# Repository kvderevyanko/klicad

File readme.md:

# Несущая плата ESP32 + E220, Rev.1

Текущая Rev.1 — **кандидат для предсерийной проверки**, а не производственный выпуск. Электрическая схема и трассировка завершены: 37 посадочных мест, 200 дорожек, 58 переходных отверстий, четыре медные зоны, два слоя, контур 145 × 90 мм; ERC, native DRC, соответствие схемы/платы и контракт платы проходят без ошибок и без неподключённых объектов.

## Действующая архитектура питания

\`BAT_PLUS → F1 → BAT_FUSED → J8.1 → внешний выключатель → J8.2 → BAT_SW → Q1 → BUCK_IN → TPS62133 → 5V_SYS\`.

\`D3 SMBJ10CA\` подключён между \`BAT_FUSED\` и GND. У Q1 \`DMP3130LQ-7\`: 1=\`Q1_GATE\`, 2=\`BUCK_IN\`, 3=\`BAT_SW\`.

\`5V_SYS → JP1 → VIN ESP32 DevKit\`. Обычный режим: выключатель включён, JP1 замкнут. Для сервисного USB с изоляцией: выключатель выключен, JP1 разомкнут при необходимости; JP1 не является автоматической изоляцией доменов.

\`5V_SYS → U4 TLV1117LV33 → AUX_3V3 → OLED\`. OLED питается только от \`AUX_3V3\`; \`DEVKIT_3V3\` не является питанием аксессуаров.

## Узлы и сборка

- J1/J2 — заводски устанавливаемые розетки ESP32; сам ESP32 DevKit устанавливает пользователь.
- J3 — заводски устанавливаемая розетка Samtec для одного пользовательского E220-400T22D или E220-900T22D; антенна обязана соответствовать диапазону модуля.
- J5 — заводски устанавливаемая розетка OLED; механическая совместимость конкретного OLED подтверждается на первом образце.
- J6 \`BUTTONS\` и J9 \`RGB OUT\` — пользовательские DNP-интерфейсы.
- D2, J7 и TP6…TP10 отсутствуют. TP1…TP5 — сохранённые металлизированные пробные отверстия без устанавливаемого компонента.

Электрические соединения завершены. Крепёж и разгрузка аккумуляторного кабеля сознательно отложены до корпуса/жгута или Rev.2. Генерация Gerber, сверловки, производственного BOM и CPL разрешается только отдельной задачей после предсерийного ревью.

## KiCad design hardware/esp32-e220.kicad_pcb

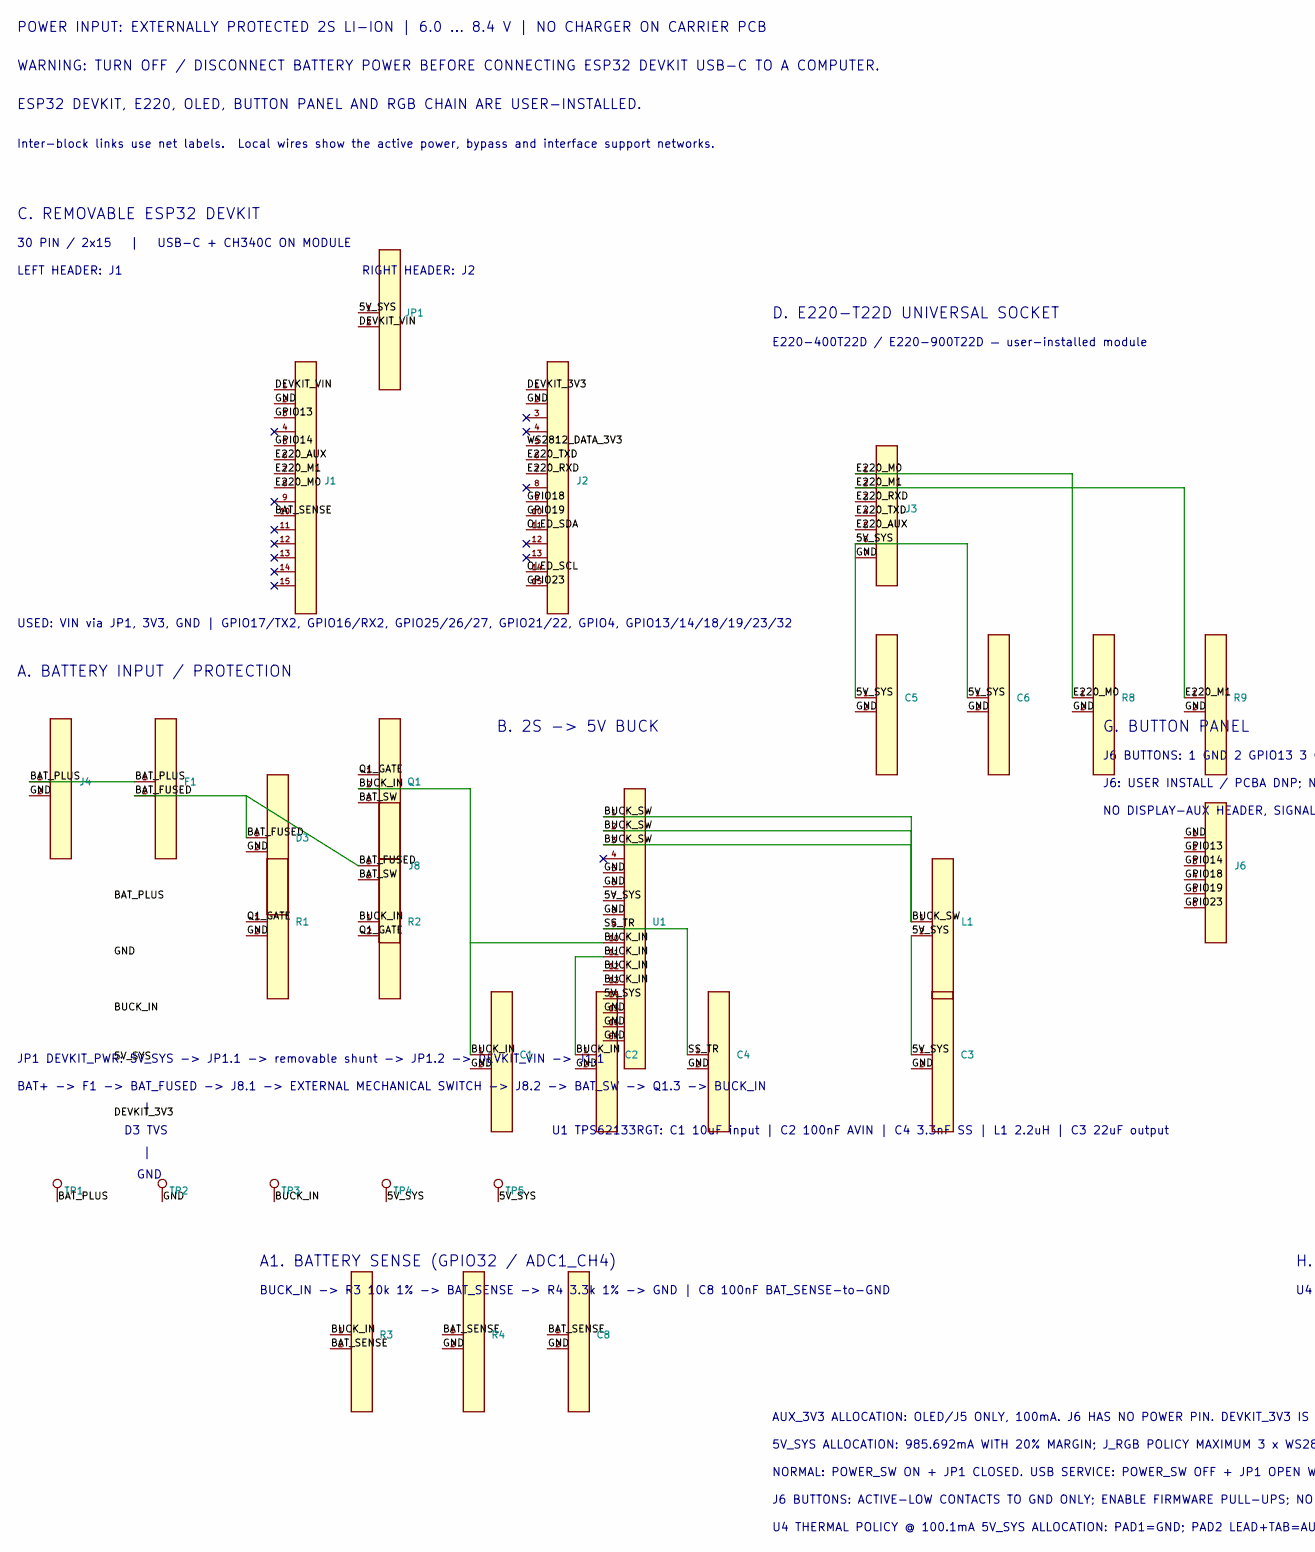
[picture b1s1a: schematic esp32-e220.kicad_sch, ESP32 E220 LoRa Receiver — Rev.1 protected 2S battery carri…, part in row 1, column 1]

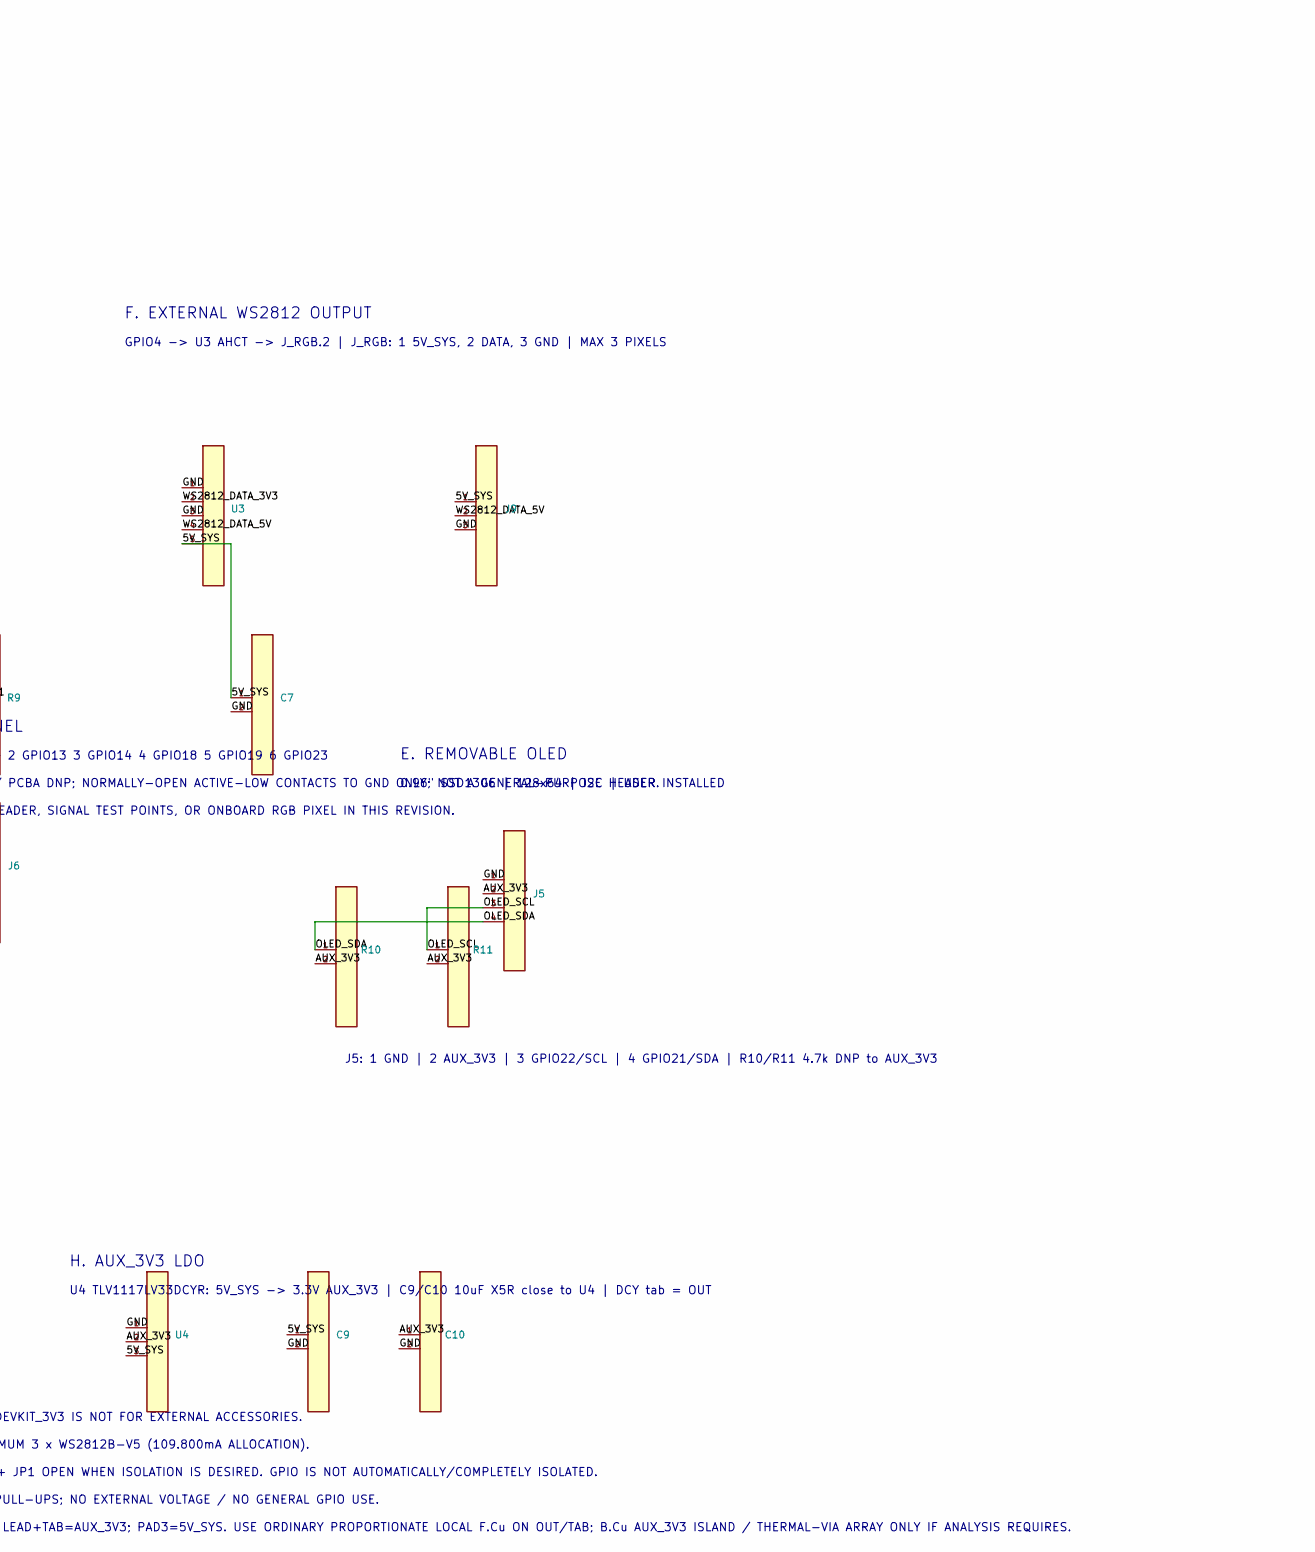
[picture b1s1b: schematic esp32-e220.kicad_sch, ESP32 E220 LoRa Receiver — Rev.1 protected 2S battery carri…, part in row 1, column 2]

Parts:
C1, C9, C10: GRM21BR61E106KA73; Murata_GRM21_2012Metric
C2, C6, C7, C8: GRM188R71C104KA01D; Murata_GRM188_1608Metric
C3: GRM21BR61A226ME44; Murata_GRM21_2012Metric
C4: GRM1885C1H332JA01D; Murata_GRM188_1608Metric
C5: GRM188R61A106MAAL; Murata_GRM188_1608Metric
D3: SMBJ10CA; Littelfuse_SMBJ10CA_DO214AA
F1: 1812L200/16; Littelfuse_1812L200_16_4532Metric
J1: SSW-115-02-G-S DEVKIT LEFT; Samtec_SSW_1x15_P2.54mm_THT
J2: SSW-115-02-G-S DEVKIT RIGHT; Samtec_SSW_1x15_P2.54mm_THT
J3: E220-400T22D / E220-900T22D SOCKET; E220_T22D_Socket_400_900
J4, J8: B2B-XH-A; JST_B2B-XH-A_1x02_P2.50mm_THT
J5: SSW-104-02-G-S; Samtec_SSW_1x04_P2.54mm_THT
J6: BUTTONS 1x6 2.54mm DNP; PinHeader_1x06_P2.54mm_Vertical
J9: J_RGB / RGB OUT 1x3 2.54mm DNP; PinHeader_1x03_P2.54mm_Vertical
JP1: TSW-102-07-G-S + SNT-100-BK-G; PinHeader_1x02_P2.54mm_Vertical
L1: XFL4020-222MEB; Coilcraft_XFL4020-222MEB
Q1: DMP3130LQ-7; Diodes_DMP3130LQ-7_SOT23
R1: 100k 1%; Resistor_0603_1608Metric
R2: 1M 1%; Resistor_0603_1608Metric
R3: RC0603FR-0710KL; Resistor_0603_1608Metric
R4: RC0603FR-073K3L; Resistor_0603_1608Metric
R8, R9: 10k 1%; Resistor_0603_1608Metric
R10: DNP 4.7k 1% OLED SDA pull-up to AUX_3V3
R11: DNP 4.7k 1% OLED SCL pull-up to AUX_3V3
TP1: BAT_PLUS; TestPoint_THT_1p0mm_PROTOTYPE
TP2: GND; TestPoint_THT_1p0mm_PROTOTYPE
TP3: BUCK_IN; TestPoint_THT_1p0mm_PROTOTYPE
TP4, TP5: 5V_SYS; TestPoint_THT_1p0mm_PROTOTYPE
U1: TPS62133RGT; TI_TPS62133RGT_RGT0016C
U3: SN74AHCT1G125DBVR; TI_SN74AHCT1G125DBVR_SOT23-5
U4: TLV1117LV33DCYR; SOT-223-3_TabPin2

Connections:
/AUX_3V3: C10.1, J5.2 (VCC / 3V3), R10.2, R11.2, U4.2 (OUT / TAB)
/BAT_FUSED: D3.1 (A), F1.2, J8.1 (BAT_FUSED)
/BAT_PLUS: F1.1, J4.1 (BAT+), TP1.1
/BAT_SENSE: C8.1, J1.10 (GPIO32), R3.2, R4.1
/BAT_SW: J8.2 (BAT_SW), Q1.3 (D)
/BUCK_IN: C1.1, C2.1, Q1.2 (S), R2.1, R3.1, TP3.1, U1.10 (AVIN), U1.11 (PVIN), U1.12 (PVIN), U1.13 (EN)
/BUCK_SW: L1.1, U1.1 (SW), U1.2 (SW), U1.3 (SW)
/DEVKIT_3V3: J2.1 (3V3)
/DEVKIT_VIN: J1.1 (VIN / 5V), JP1.2 (DEVKIT_VIN)
/E220_AUX: J1.6 (GPIO27), J3.5 (AUX)
/E220_M0: J1.8 (GPIO25), J3.1 (M0), R8.1
/E220_M1: J1.7 (GPIO26), J3.2 (M1), R9.1
/E220_RXD: J2.7 (GPIO17/TX2), J3.3 (RXD)
/E220_TXD: J2.6 (GPIO16/RX2), J3.4 (TXD)
/GPIO13: J1.3 (GPIO13), J6.2 (GPIO13)
/GPIO14: J1.5 (GPIO14), J6.3 (GPIO14)
/GPIO18: J2.9 (GPIO18), J6.4 (GPIO18)
/GPIO19: J2.10 (GPIO19), J6.5 (GPIO19)
/GPIO23: J2.15 (GPIO23), J6.6 (GPIO23)
/OLED_SCL: J2.14 (GPIO22), J5.3 (SCL), R11.1
/OLED_SDA: J2.11 (GPIO21), J5.4 (SDA), R10.1
/Q1_GATE: Q1.1 (G), R1.1, R2.2
/SS_TR: C4.1, U1.9 (SS/TR)
/WS2812_DATA_3V3: J2.5 (GPIO4), U3.2 (A)
/WS2812_DATA_5V: J9.2 (WS2812_DATA_5V), U3.4 (Y)

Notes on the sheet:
A. BATTERY INPUT / PROTECTION
B. 2S -> 5V BUCK
H. AUX_3V3 LDO
U4 TLV1117LV33DCYR: 5V_SYS -> 3.3V AUX_3V3 | C9/C10 10uF X5R close to U4 | DCY tab = OUT
AUX_3V3 ALLOCATION: OLED/J5 ONLY, 100mA. J6 HAS NO POWER PIN. DEVKIT_3V3 IS NOT FOR EXTERNAL ACCESSORIES.
5V_SYS ALLOCATION: 985.692mA WITH 20% MARGIN; J_RGB POLICY MAXIMUM 3 x WS2812B-V5 (109.800mA ALLOCATION).
NORMAL: POWER_SW ON + JP1 CLOSED. USB SERVICE: POWER_SW OFF + JP1 OPEN WHEN ISOLATION IS DESIRED. GPIO IS NOT AUTOMATICALLY/COMPLETELY ISOLATED.
J6 BUTTONS: ACTIVE-LOW CONTACTS TO GND ONLY; ENABLE FIRMWARE PULL-UPS; NO EXTERNAL VOLTAGE / NO GENERAL GPIO USE.
U4 THERMAL POLICY @ 100.1mA 5V_SYS ALLOCATION: PAD1=GND; PAD2 LEAD+TAB=AUX_3V3; PAD3=5V_SYS. USE ORDINARY PROPORTIONATE LOCAL F.Cu ON OUT/TAB; B.Cu AUX_3V3 ISLAND / THERMAL-VIA ARRAY ONLY IF ANALYSIS REQUIRES.
A1. BATTERY SENSE (GPIO32 / ADC1_CH4)
BUCK_IN -> R3 10k 1% -> BAT_SENSE -> R4 3.3k 1% -> GND | C8 100nF BAT_SENSE-to-GND
C. REMOVABLE ESP32 DEVKIT
30 PIN / 2x15 | USB-C + CH340C ON MODULE
LEFT HEADER: J1 RIGHT HEADER: J2
USED: VIN via JP1, 3V3, GND | GPIO17/TX2, GPIO16/RX2, GPIO25/26/27, GPIO21/22, GPIO4, GPIO13/14/18/19/23/32
D. E220-T22D UNIVERSAL SOCKET
E220-400T22D / E220-900T22D — user-installed module
F. EXTERNAL WS2812 OUTPUT
GPIO4 -> U3 AHCT -> J_RGB.2 | J_RGB: 1 5V_SYS, 2 DATA, 3 GND | MAX 3 PIXELS
E. REMOVABLE OLED
0.96" SSD1306 | 128x64 | I2C | USER INSTALLED
POWER INPUT: EXTERNALLY PROTECTED 2S LI-ION | 6.0 ... 8.4 V | NO CHARGER ON CARRIER PCB
WARNING: TURN OFF / DISCONNECT BATTERY POWER BEFORE CONNECTING ESP32 DEVKIT USB-C TO A COMPUTER.
ESP32 DEVKIT, E220, OLED, BUTTON PANEL AND RGB CHAIN ARE USER-INSTALLED.
Inter-block links use net labels. Local wires show the active power, bypass and interface support networks.
G. BUTTON PANEL
J6 BUTTONS: 1 GND 2 GPIO13 3 GPIO14 4 GPIO18 5 GPIO19 6 GPIO23
J6: USER INSTALL / PCBA DNP; NORMALLY-OPEN ACTIVE-LOW CONTACTS TO GND ONLY; NOT A GENERAL-PURPOSE HEADER.
NO DISPLAY-AUX HEADER, SIGNAL TEST POINTS, OR ONBOARD RGB PIXEL IN THIS REVISION.
JP1 DEVKIT_PWR: 5V_SYS -> JP1.1 -> removable shunt -> JP1.2 -> DEVKIT_VIN -> J1.1
BAT+ -> F1 -> BAT_FUSED -> J8.1 -> EXTERNAL MECHANICAL SWITCH -> J8.2 -> BAT_SW -> Q1.3 -> BUCK_IN
D3 TVS
GND
U1 TPS62133RGT: C1 10uF input | C2 100nF AVIN | C4 3.3nF SS | L1 2.2uH | C3 22uF output
J5: 1 GND | 2 AUX_3V3 | 3 GPIO22/SCL | 4 GPIO21/SDA | R10/R11 4.7k DNP to AUX_3V3

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
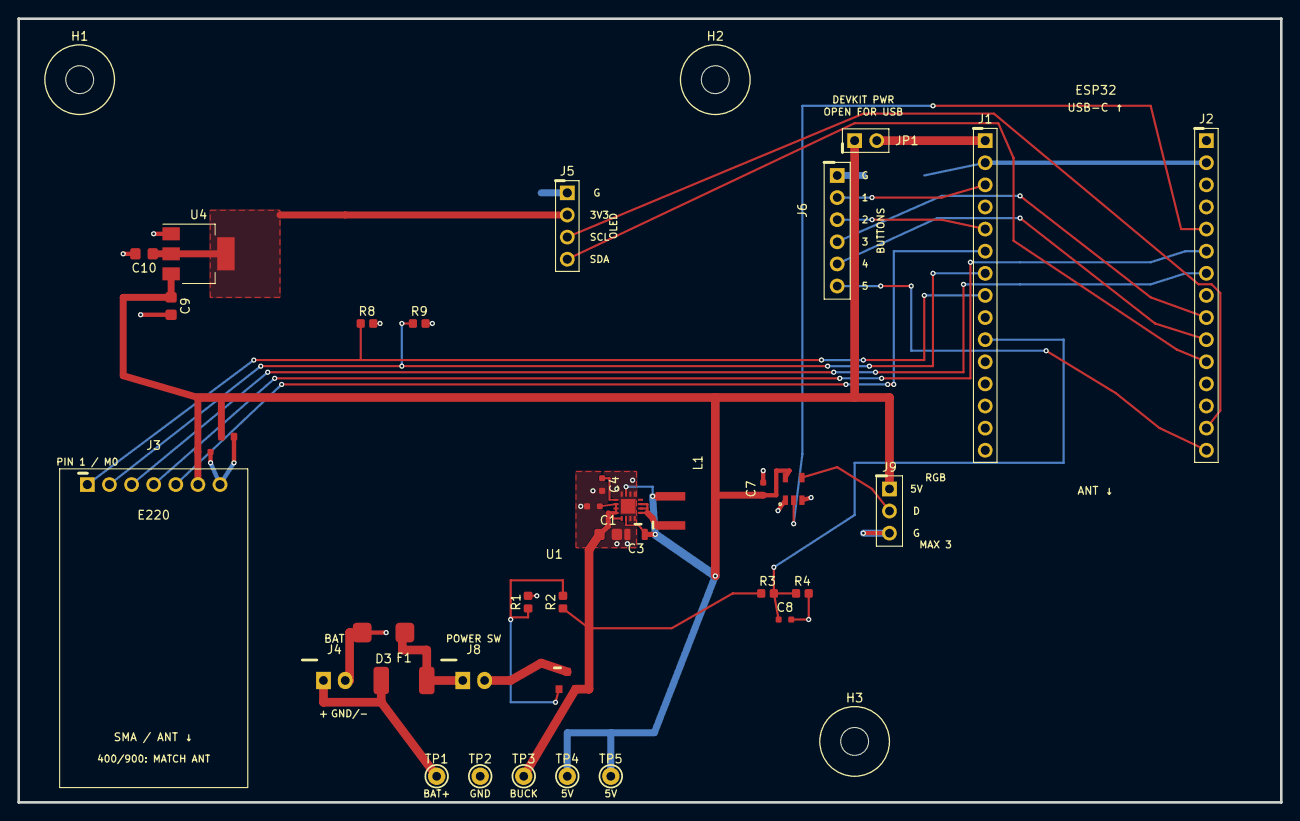
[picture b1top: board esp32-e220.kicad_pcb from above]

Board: 2 copper layers, 145.0 x 90.0 mm, 40 parts (0 on the bottom side), 26 nets.

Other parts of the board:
H1, H2, H3: M3 NPTH; MountingHole_M3_NPTH_REV1

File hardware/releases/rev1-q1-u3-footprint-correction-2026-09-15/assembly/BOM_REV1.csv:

Item,Qty,References,Value,Manufacturer,MPN,Footprint,AssemblyClass,ProcurementPolicy,Notes
1,1,R1,100k 1%,,,Resistor_0603_1608Metric,PCBA_POPULATE,APPROVED_GENERIC,
2,2,"R8, R9",10k 1%,,,Resistor_0603_1608Metric,PCBA_POPULATE,APPROVED_GENERIC,
3,1,F1,1812L200/16,Littelfuse,1812L200/16,Littelfuse_1812L200_16_4532Metric,PCBA_POPULATE,EXACT_MPN,
4,1,R2,1M 1%,,,Resistor_0603_1608Metric,PCBA_POPULATE,APPROVED_GENERIC,
5,2,"J4, J8",B2B-XH-A,JST,B2B-XH-A,JST_B2B-XH-A_1x02_P2.50mm_THT,PCBA_POPULATE,EXACT_MPN,
6,1,Q1,DMP3130LQ-7,Diodes Incorporated,DMP3130LQ-7,Diodes_DMP3130LQ-7_SOT23,PCBA_POPULATE,EXACT_MPN,
7,1,J3,E220-400T22D / E220-900T22D SOCKET,Samtec,SSW-107-02-G-S,E220_T22D_Socket_400_900,PCBA_POPULATE,EXACT_MPN,"E220 carrier socket, not E220 module"
8,1,C4,GRM1885C1H332JA01D,Murata,GRM1885C1H332JA01D,Murata_GRM188_1608Metric,PCBA_POPULATE,EXACT_MPN,
9,1,C5,GRM188R61A106MAAL,Murata,GRM188R61A106MAAL,Murata_GRM188_1608Metric,PCBA_POPULATE,EXACT_MPN,
10,1,C8,GRM188R71C104KA01D,Murata,GRM188R71C104KA01D,Carrier:Murata_GRM188_1608Metric,PCBA_POPULATE,EXACT_MPN,
11,3,"C2, C6, C7",GRM188R71C104KA01D,Murata,GRM188R71C104KA01D,Murata_GRM188_1608Metric,PCBA_POPULATE,EXACT_MPN,
12,1,C3,GRM21BR61A226ME44,Murata,GRM21BR61A226ME44,Murata_GRM21_2012Metric,PCBA_POPULATE,EXACT_MPN,
13,2,"C10, C9",GRM21BR61E106KA73,Murata,GRM21BR61E106KA73,Carrier:Murata_GRM21_2012Metric,PCBA_POPULATE,EXACT_MPN,
14,1,C1,GRM21BR61E106KA73,Murata,GRM21BR61E106KA73,Murata_GRM21_2012Metric,PCBA_POPULATE,EXACT_MPN,
15,1,R3,RC0603FR-0710KL,Yageo,RC0603FR-0710KL,Carrier:Resistor_0603_1608Metric,PCBA_POPULATE,EXACT_MPN,
16,1,R4,RC0603FR-073K3L,Yageo,RC0603FR-073K3L,Carrier:Resistor_0603_1608Metric,PCBA_POPULATE,EXACT_MPN,
17,1,D3,SMBJ10CA,Littelfuse,SMBJ10CA,Littelfuse_SMBJ10CA_DO214AA,PCBA_POPULATE,EXACT_MPN,
18,1,U3,SN74AHCT1G125DBVR,Texas Instruments,SN74AHCT1G125DBVR,TI_SN74AHCT1G125DBVR_SOT23-5,PCBA_POPULATE,EXACT_MPN,
19,1,J5,SSW-104-02-G-S,Samtec,SSW-104-02-G-S,Samtec_SSW_1x04_P2.54mm_THT,PCBA_POPULATE,EXACT_MPN,"OLED carrier socket, not OLED module"
20,1,J1,SSW-115-02-G-S DEVKIT LEFT,Samtec,SSW-115-02-G-S,Samtec_SSW_1x15_P2.54mm_THT,PCBA_POPULATE,EXACT_MPN,"ESP32 carrier socket, not module"
21,1,J2,SSW-115-02-G-S DEVKIT RIGHT,Samtec,SSW-115-02-G-S,Samtec_SSW_1x15_P2.54mm_THT,PCBA_POPULATE,EXACT_MPN,"ESP32 carrier socket, not module"
22,1,U4,TLV1117LV33DCYR,Texas Instruments,TLV1117LV33DCYR,Package_TO_SOT_SMD:SOT-223-3_TabPin2,PCBA_POPULATE,EXACT_MPN,
23,1,U1,TPS62133RGT,Texas Instruments,TPS62133RGT,TI_TPS62133RGT_RGT0016C,PCBA_POPULATE,EXACT_MPN,
24,1,JP1,TSW-102-07-G-S + SNT-100-BK-G,Samtec,TSW-102-07-G-S,Connector_PinHeader_2.54mm:PinHeader_1x02_P2.54mm_Vertical,PCBA_POPULATE,EXACT_MPN,2-pin header only
25,1,L1,XFL4020-222MEB,Coilcraft,XFL4020-222MEB,Coilcraft_XFL4020-222MEB,PCBA_POPULATE,EXACT_MPN,

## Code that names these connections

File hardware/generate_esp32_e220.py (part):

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def pin_no_connect(center_x, center_y, pin_count, pin_number):
    return no_connect(*pin_pos(center_x, center_y, pin_count, pin_number))

left = [("1","VIN / 5V"),("2","GND"),("3","GPIO13"),("4","GPIO12"),("5","GPIO14"),
        ("6","GPIO27"),("7","GPIO26"),("8","GPIO25"),("9","GPIO33"),("10","GPIO32"),
        ("11","GPIO35"),("12","GPIO34"),("13","GPIO39/VN"),("14","GPIO36/VP"),("15","EN")]
right = [("1","3V3"),("2","GND"),("3","GPIO15"),("4","GPIO2"),("5","GPIO4"),
         ("6","GPIO16/RX2"),("7","GPIO17/TX2"),("8","GPIO5"),("9","GPIO18"),("10","GPIO19"),
         ("11","GPIO21"),("12","GPIO3/RX0"),("13","GPIO1/TX0"),("14","GPIO22"),("15","GPIO23")]
e220 = [("1","M0","input"),("2","M1","input"),("3","RXD","input"),
        ("4","TXD","output"),("5","AUX","output"),("6","VCC","power_in"),("7","GND","power_in")]
oled_i2c = [("1","GND","power_in"),("2","VCC / 3V3","power_in"),
            ("3","SCL","bidirectional"),("4","SDA","bidirectional")]
battery = [("1","BAT+","passive"),("2","BAT-","passive")]
buttons = [("1","GND"),("2","GPIO13"),("3","GPIO14"),("4","GPIO18"),
           ("5","GPIO19"),("6","GPIO23")]
rgb_out = [("1","5V_SYS"),("2","WS2812_DATA_5V"),("3","GND")]
power_switch = [("1","BAT_FUSED"),("2","BAT_SW")]
devkit_pwr = [("1","5V_SYS"),("2","DEVKIT_VIN")]
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    items.append(instance(a,b,c,d,e,f,dnp=b in {"R10", "R11"}))

# Verified DevKit/E220/LED signals retained from Stage 5 plus authorized Rev.1 expansion.
for n, net in [(1,"DEVKIT_VIN"),(2,"GND"),(3,"GPIO13"),(5,"GPIO14"),(6,"E220_AUX"),(7,"E220_M1"),(8,"E220_M0"),
               (10,"BAT_SENSE")]:
    items.append(pin_label(70,100,len(left),n,net))
for n in set(range(1,16)) - {1,2,3,5,6,7,8,10}: items.append(pin_no_connect(70,100,len(left),n))
for n, net in [(1,"DEVKIT_3V3"),(2,"GND"),(5,"WS2812_DATA_3V3"),(6,"E220_TXD"),(7,"E220_RXD"),
               (9,"GPIO18"),(10,"GPIO19"),(15,"GPIO23")]:
    items.append(pin_label(115,100,len(right),n,net))
# One-sheet I2C nets: local labels intentionally connect DevKit, socket and
# optional pull-up sites without creating a global-label/local-label ERC mix.
items += [label("OLED_SDA", *pin_pos(115,100,len(right),11)), label("OLED_SCL", *pin_pos(115,100,len(right),14))]
for n in set(range(1,16)) - {1,2,5,6,7,9,10,11,14,15}: items.append(pin_no_connect(115,100,len(right),n))
for n, net in [(1,"E220_M0"),(2,"E220_M1"),(3,"E220_RXD"),(4,"E220_TXD"),(5,"E220_AUX"),(6,"5V_SYS"),(7,"GND")]:
    items.append(pin_label(175,105,len(e220),n,net))
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    items.append(pin_label(330,175,len(oled_i2c),n,net))

# Battery connector, switch and protection: the P-MOS body diode must precharge from
# BAT_SW (D, pin 3) to BUCK_IN (S, pin 2). Correct polarity then produces
# negative VGS and enhanced conduction; reversed pack polarity leaves the body
# diode reverse-biased and VGS non-negative. D3 is across BAT_FUSED/GND.
items += [pin_label(25,155,len(battery),1,"BAT_PLUS"), pin_label(25,155,len(battery),2,"GND"),
          pin_label(45,155,len(fuse),1,"BAT_PLUS"), pin_label(45,155,len(fuse),2,"BAT_FUSED"),
          pin_label(65,165,len(tvs),1,"BAT_FUSED"), pin_label(65,165,len(tvs),2,"GND"),
          pin_label(85,170,len(power_switch),1,"BAT_FUSED"), pin_label(85,170,len(power_switch),2,"BAT_SW"),
          pin_label(85,155,len(pmos),1,"Q1_GATE"), pin_label(85,155,len(pmos),2,"BUCK_IN"), pin_label(85,155,len(pmos),3,"BAT_SW")]

# DEVKIT_PWR intentionally creates two separate nets: a removable shunt is the
# only approved connection from 5V_SYS to the DevKit VIN pad.
items += [pin_label(85,70,len(devkit_pwr),1,"5V_SYS"), pin_label(85,70,len(devkit_pwr),2,"DEVKIT_VIN")]

# BAT_SENSE is a strictly local divider from BUCK_IN to ADC1 GPIO32.  C8 is the
# Espressif-recommended 100-nF ADC-input filter capacitor.
items += [pin_label(80,255,2,1,"BUCK_IN"), pin_label(80,255,2,2,"BAT_SENSE"),
          pin_label(100,255,2,1,"BAT_SENSE"), pin_label(100,255,2,2,"GND"),
          pin_label(120,255,2,1,"BAT_SENSE"), pin_label(120,255,2,2,"GND")]

# J6 is not a general GPIO expansion port.  It is a DNP panel-button interface:
# firmware enables pull-ups and each external normally-open contact shorts one
# signal to J6.1/GND when pressed.  No external voltage may be applied.
for n, net in [(1,"GND"),(2,"GPIO13"),(3,"GPIO14"),(4,"GPIO18"),(5,"GPIO19"),(6,"GPIO23")]:
    items.append(pin_label(235,170,len(buttons),n,net))

# External RGB output only.  WorldSemi's WS2812B-V5 primary data gives VIH >=
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               (13,"BUCK_IN"),(14,"5V_SYS"),(15,"GND"),(16,"GND"),(17,"GND")]:
    items.append(pin_label(130,180,len(tps62133),n,net))
items.append(pin_no_connect(130,180,len(tps62133),4))
items += [pin_label(185,180,len(inductor),1,"BUCK_SW"), pin_label(185,180,len(inductor),2,"5V_SYS")]

for n, net in [(1,"GND"),(2,"WS2812_DATA_3V3"),(3,"GND"),(4,"WS2812_DATA_5V"),(5,"5V_SYS")]: items.append(pin_label(275,105,len(ahct),n,net))

# U4 is the only authorized source of AUX_3V3.  The DCY tab is electrically
# identical to pin 2 and is therefore explicitly represented as AUX_3V3.
items += [pin_label(265,255,len(tlv1117lv33),1,"GND"), pin_label(265,255,len(tlv1117lv33),2,"AUX_3V3"),
          pin_label(265,255,len(tlv1117lv33),3,"5V_SYS"),
          pin_label(295,255,2,1,"5V_SYS"), pin_label(295,255,2,2,"GND"),
          pin_label(315,255,2,1,"AUX_3V3"), pin_label(315,255,2,2,"GND")]

for ref, x, y, net in [("TP1",25,230,"BAT_PLUS"),("TP2",45,230,"GND"),("TP3",65,230,"BUCK_IN"),("TP4",85,230,"5V_SYS"),("TP5",105,230,"5V_SYS")]: items.append(label(net,x,y))

# ERC source markers: external protected battery/return plus the explicitly
# declared protected BUCK_IN and U1-generated 5V_SYS domains.
items += [label("BAT_PLUS",35,175), label("GND",35,185), label("BUCK_IN",35,195), label("5V_SYS",35,205), label("DEVKIT_3V3",35,215)]

for x,y,a,b in [(65,180,"Q1_GATE","GND"),(85,180,"BUCK_IN","Q1_GATE"),(105,205,"BUCK_IN","GND"),(125,205,"BUCK_IN","GND"),
                (145,205,"SS_TR","GND"),(185,205,"5V_SYS","GND"),(175,140,"5V_SYS","GND"),(195,140,"5V_SYS","GND"),
                (215,140,"E220_M0","GND"),(235,140,"E220_M1","GND"),(285,140,"5V_SYS","GND"),
                (300,185,"OLED_SDA","AUX_3V3"),(320,185,"OLED_SCL","AUX_3V3")]: items += [pin_label(x,y,2,1,a),pin_label(x,y,2,2,b)]

items += [
    # Functional-block headers deliberately contain the operational information
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    heading("B. 2S -> 5V BUCK", 105, 145),
    heading("H. AUX_3V3 LDO", 250, 242),
    note("U4 TLV1117LV33DCYR: 5V_SYS -> 3.3V AUX_3V3 | C9/C10 10uF X5R close to U4 | DCY tab = OUT", 250, 247),
    note("AUX_3V3 ALLOCATION: OLED/J5 ONLY, 100mA. J6 HAS NO POWER PIN. DEVKIT_3V3 IS NOT FOR EXTERNAL ACCESSORIES.", 155, 270),
    note("5V_SYS ALLOCATION: 985.692mA WITH 20% MARGIN; J_RGB POLICY MAXIMUM 3 x WS2812B-V5 (109.800mA ALLOCATION).", 155, 275),
    note("NORMAL: POWER_SW ON + JP1 CLOSED. USB SERVICE: POWER_SW OFF + JP1 OPEN WHEN ISOLATION IS DESIRED. GPIO IS NOT AUTOMATICALLY/COMPLETELY ISOLATED.", 155, 280),
    note("J6 BUTTONS: ACTIVE-LOW CONTACTS TO GND ONLY; ENABLE FIRMWARE PULL-UPS; NO EXTERNAL VOLTAGE / NO GENERAL GPIO USE.", 155, 285),
    note("U4 THERMAL POLICY @ 100.1mA 5V_SYS ALLOCATION: PAD1=GND; PAD2 LEAD+TAB=AUX_3V3; PAD3=5V_SYS. USE ORDINARY PROPORTIONATE LOCAL F.Cu ON OUT/TAB; B.Cu AUX_3V3 ISLAND / THERMAL-VIA ARRAY ONLY IF ANALYSIS REQUIRES.", 155, 290),
    heading("A1. BATTERY SENSE (GPIO32 / ADC1_CH4)", 62, 242),
    note("BUCK_IN -> R3 10k 1% -> BAT_SENSE -> R4 3.3k 1% -> GND | C8 100nF BAT_SENSE-to-GND", 62, 247),
    heading("C. REMOVABLE ESP32 DEVKIT", 18, 52),
    note("30 PIN / 2x15   |   USB-C + CH340C ON MODULE", 18, 57),
    note("LEFT HEADER: J1                                      RIGHT HEADER: J2", 18, 62),
    note("USED: VIN via JP1, 3V3, GND | GPIO17/TX2, GPIO16/RX2, GPIO25/26/27, GPIO21/22, GPIO4, GPIO13/14/18/19/23/32", 18, 126),
    heading("D. E220-T22D UNIVERSAL SOCKET", 155, 70),
    note("E220-400T22D / E220-900T22D — user-installed module", 155, 75),
    heading("F. EXTERNAL WS2812 OUTPUT", 260, 70),
    note("GPIO4 -> U3 AHCT -> J_RGB.2 | J_RGB: 1 5V_SYS, 2 DATA, 3 GND | MAX 3 PIXELS", 260, 75),
    heading("E. REMOVABLE OLED", 310, 150),
    note("0.96\" SSD1306 | 128x64 | I2C | USER INSTALLED", 310, 155),
    note("POWER INPUT: EXTERNALLY PROTECTED 2S LI-ION | 6.0 ... 8.4 V | NO CHARGER ON CARRIER PCB", 18, 18, 1.8),
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    note("ESP32 DEVKIT, E220, OLED, BUTTON PANEL AND RGB CHAIN ARE USER-INSTALLED.", 18, 32, 1.8),
    note("Inter-block links use net labels.  Local wires show the active power, bypass and interface support networks.", 18, 39),
    heading("G. BUTTON PANEL", 215, 145),
    note("J6 BUTTONS: 1 GND 2 GPIO13 3 GPIO14 4 GPIO18 5 GPIO19 6 GPIO23", 215, 150),
    note("J6: USER INSTALL / PCBA DNP; NORMALLY-OPEN ACTIVE-LOW CONTACTS TO GND ONLY; NOT A GENERAL-PURPOSE HEADER.", 215, 155),
    note("NO DISPLAY-AUX HEADER, SIGNAL TEST POINTS, OR ONBOARD RGB PIXEL IN THIS REVISION.", 215, 160),
    note("JP1 DEVKIT_PWR: 5V_SYS -> JP1.1 -> removable shunt -> JP1.2 -> DEVKIT_VIN -> J1.1", 18, 205),
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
